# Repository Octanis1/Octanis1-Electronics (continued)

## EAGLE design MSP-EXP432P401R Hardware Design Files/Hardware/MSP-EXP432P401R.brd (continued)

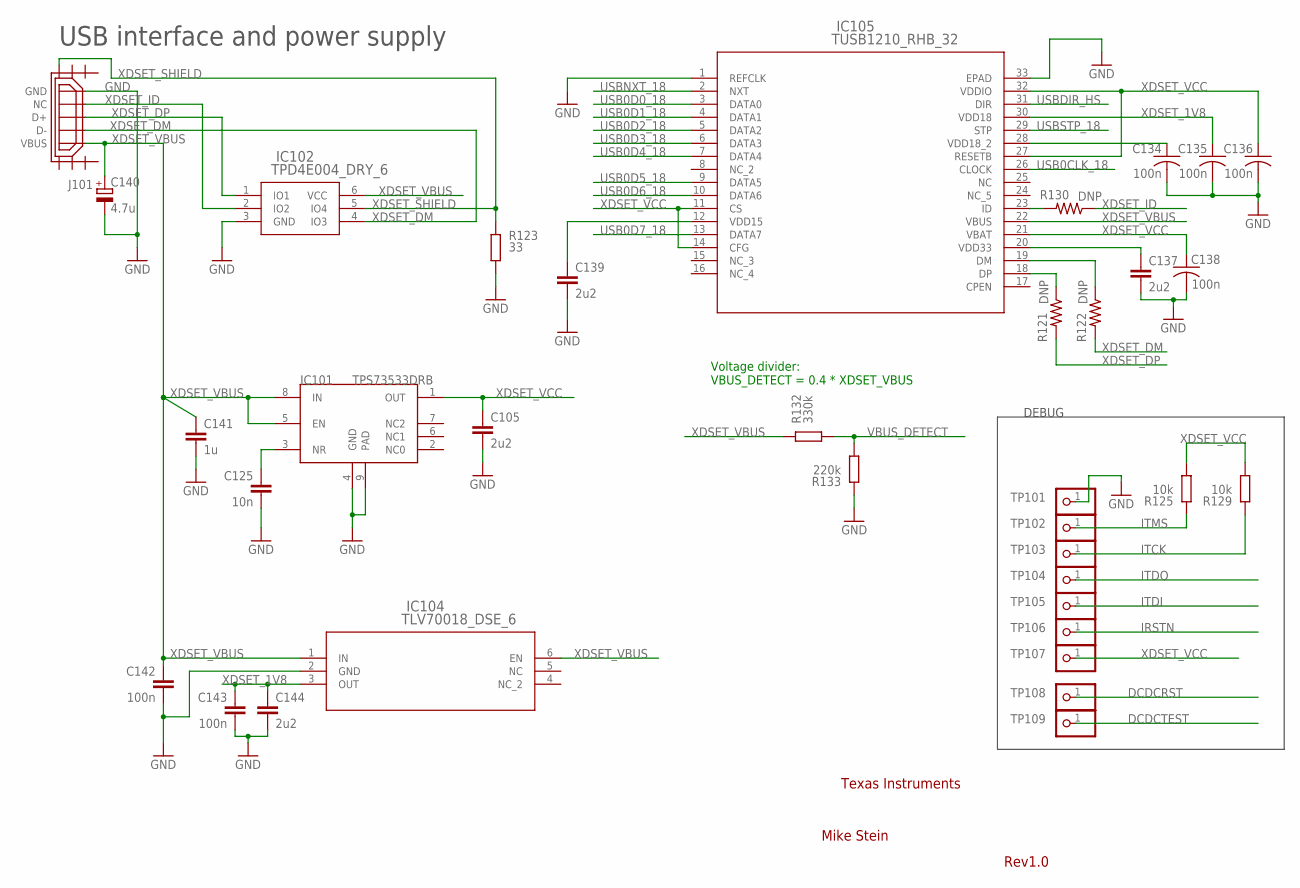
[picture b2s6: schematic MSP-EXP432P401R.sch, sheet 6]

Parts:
C105, C137, C139, C144: 2u2; C0603
C125: 10n; 0402
C134, C135, C136, C138: 100n; C0402
C140: 4.7u; A/3216-18R
C141: 1u; C0603
C142, C143: 100n; 0402
IC101: TPS73533DRB; SON8
IC102: TPD4E004_DRY_6; DRY6
IC104: TLV70018_DSE_6; DSE6
IC105: TUSB1210_RHB_32; RHB32_3P45X3P45
J101: USB_MICRO_FLIPPED; HIROSE-ZX62R-B-5P
R121, R122, R130: DNP; R0402
R123: 33; 0402
R125, R129: 10k; 0402
R132: 330k; 0402
R133: 220k; 0402
TP101, TP102, TP103, TP104, TP105, TP106, TP107, TP108, TP109: TEST_PIN2; 1X01

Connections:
DCDCRST: TP108.1; also elsewhere on the board
DCDCTEST: TP109.1; also elsewhere on the board
GND: C105.2, C125.2, C134.2, C135.2, C136.2, C137.2, C138.2, C139.2, C140.-, C141.2, C142.2, C143.2, C144.2, IC101.4 (GND), IC101.9 (PAD), IC102.3 (GND), IC104.2 (GND), IC105.1 (REFCLK), IC105.33 (EPAD), J101.GND, R123.2, R133.1, TP101.1; also elsewhere on the board
IRSTN: TP106.1; also elsewhere on the board
ITCK: R129.1, TP103.1; also elsewhere on the board
ITDI: TP105.1; also elsewhere on the board
ITDO: TP104.1; also elsewhere on the board
ITMS: R125.1, TP102.1; also elsewhere on the board
unnamed: IC105.18 (DP), R121.1
unnamed: IC105.19 (DM), R122.1
unnamed: C125.1, IC101.3 (NR)
unnamed: C137.1, IC105.20 (VDD33)
unnamed: C139.1, IC105.12 (VDD15)
unnamed: C134.1, IC105.28 (VDD18_2)
USB0CLK_18: IC105.26 (CLOCK); also elsewhere on the board
USB0D0_18: IC105.3 (DATA0); also elsewhere on the board
USB0D1_18: IC105.4 (DATA1); also elsewhere on the board
USB0D2_18: IC105.5 (DATA2); also elsewhere on the board
USB0D3_18: IC105.6 (DATA3); also elsewhere on the board
USB0D4_18: IC105.7 (DATA4); also elsewhere on the board
USB0D5_18: IC105.9 (DATA5); also elsewhere on the board
USB0D6_18: IC105.10 (DATA6); also elsewhere on the board
USB0D7_18: IC105.13 (DATA7); also elsewhere on the board
USBDIR_HS: IC105.31 (DIR); also elsewhere on the board
USBNXT_18: IC105.2 (NXT); also elsewhere on the board
USBSTP_18: IC105.29 (STP); also elsewhere on the board
VBUS_DETECT: R132.2, R133.2; also elsewhere on the board
XDSET_1V8: C135.1, C143.1, C144.1, IC104.3 (OUT), IC105.30 (VDD18); also elsewhere on the board
XDSET_DM: IC102.4 (IO3), J101.D-, R122.2; also elsewhere on the board
XDSET_DP: IC102.1 (IO1), J101.D+, R121.2; also elsewhere on the board
XDSET_ID: IC102.2 (IO2), J101.NC, R130.1; also elsewhere on the board
XDSET_IDR: IC105.23 (ID), R130.2
XDSET_SHIELD: IC102.5 (IO4), J101.SHIELD3, R123.1
XDSET_VBUS: C140.+, C141.1, C142.1, IC101.5 (EN), IC101.8 (IN), IC102.6 (VCC), IC104.1 (IN), IC104.6 (EN), IC105.22 (VBUS), J101.VBUS, R132.1; also elsewhere on the board
XDSET_VCC: C105.1, C136.1, C138.1, IC101.1 (OUT), IC105.11 (CS), IC105.14 (CFG), IC105.21 (VBAT), IC105.27 (RESETB), IC105.32 (VDDIO), R125.2, R129.2, TP107.1; also elsewhere on the board

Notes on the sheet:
USB interface and power supply
DEBUG
Voltage divider: VBUS_DETECT = 0.4 * XDSET_VBUS
Texas Instruments
Mike Stein
Rev1.0

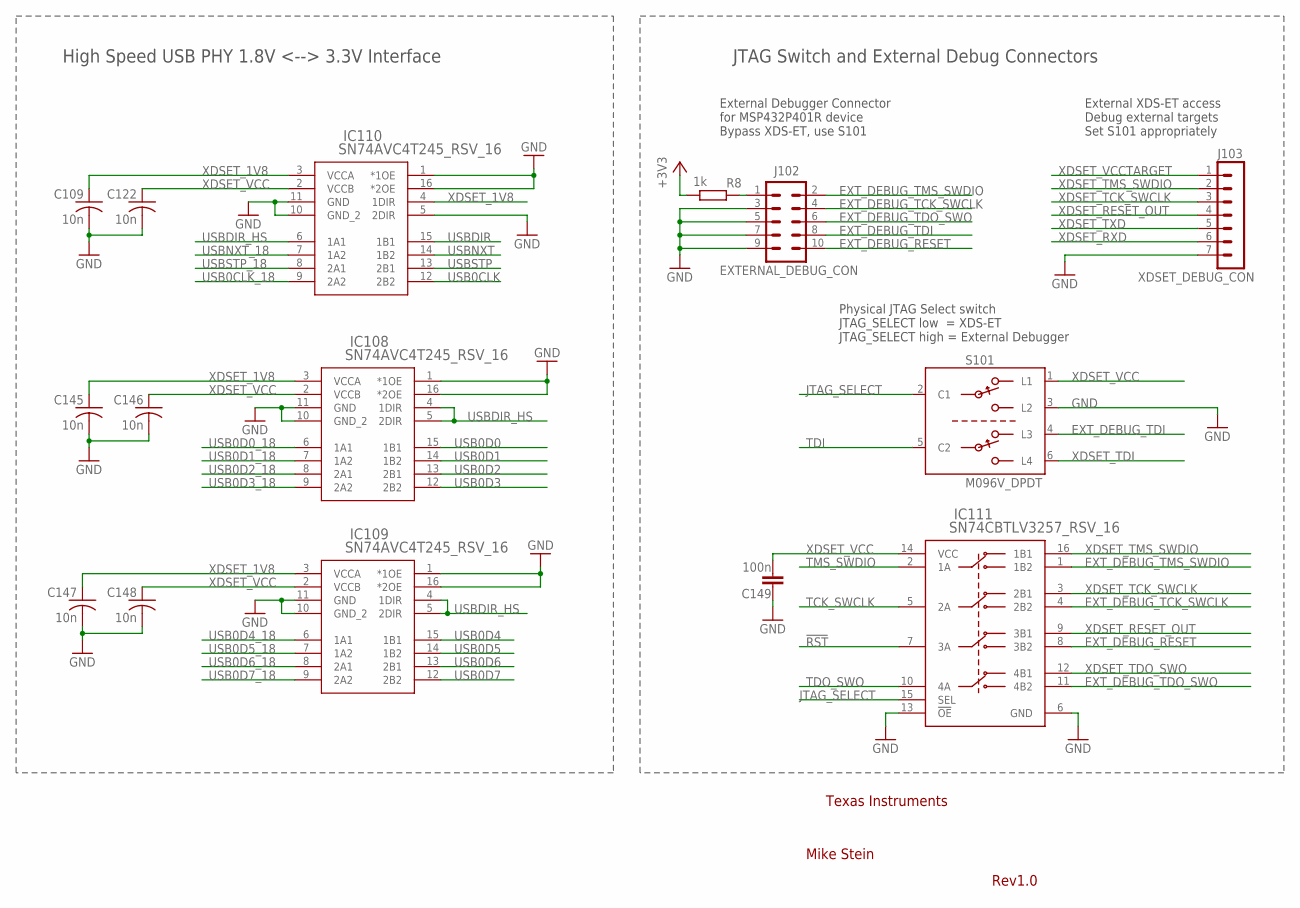
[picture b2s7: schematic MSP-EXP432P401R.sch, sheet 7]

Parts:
C109, C122, C145, C146, C147, C148: 10n; C0402
C149: 100n; 0402
IC108, IC109, IC110: SN74AVC4T245_RSV_16; RSV16
IC111: SN74CBTLV3257_RSV_16; RSV16
J102: EXTERNAL_DEBUG_CON; EXTERNAL_DEBUG
J103: XDSET_DEBUG_CON; XDSET_DEBUG
R8: 1k; 0402
S101: M096V_DPDT

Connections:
!RST: IC111.7 (3A); also elsewhere on the board
+3V3: R8.1; also elsewhere on the board
EXT_DEBUG_RESET: IC111.8 (3B2), J102.10
EXT_DEBUG_TCK_SWCLK: IC111.4 (2B2), J102.4
EXT_DEBUG_TDI: J102.8, S101.4 (L3)
EXT_DEBUG_TDO_SWO: IC111.11 (4B2), J102.6
EXT_DEBUG_TMS_SWDIO: IC111.1 (1B2), J102.2
GND: C109.2, C122.2, C145.2, C146.2, C147.2, C148.2, C149.2, IC108.1 (*1OE), IC108.10 (GND_2), IC108.11 (GND), IC108.16 (*2OE), IC109.1 (*1OE), IC109.10 (GND_2), IC109.11 (GND), IC109.16 (*2OE), IC110.1 (*1OE), IC110.5 (2DIR), IC110.10 (GND_2), IC110.11 (GND), IC110.16 (*2OE), IC111.6 (GND), IC111.13 (!OE), J102.3, J102.5, J102.7, J102.9, J103.7, S101.3 (L2); also elsewhere on the board
JTAG_SELECT: IC111.15 (SEL), S101.2 (C1)
unnamed: J102.1, R8.2
TCK_SWCLK: IC111.5 (2A); also elsewhere on the board
TDI: S101.5 (C2); also elsewhere on the board
TDO_SWO: IC111.10 (4A); also elsewhere on the board
TMS_SWDIO: IC111.2 (1A); also elsewhere on the board
USB0CLK: IC110.12 (2B2); also elsewhere on the board
USB0CLK_18: IC110.9 (2A2); also elsewhere on the board
USB0D0: IC108.15 (1B1); also elsewhere on the board
USB0D0_18: IC108.6 (1A1); also elsewhere on the board
USB0D1: IC108.14 (1B2); also elsewhere on the board
USB0D1_18: IC108.7 (1A2); also elsewhere on the board
USB0D2: IC108.13 (2B1); also elsewhere on the board
USB0D2_18: IC108.8 (2A1); also elsewhere on the board
USB0D3: IC108.12 (2B2); also elsewhere on the board
USB0D3_18: IC108.9 (2A2); also elsewhere on the board
USB0D4: IC109.15 (1B1); also elsewhere on the board
USB0D4_18: IC109.6 (1A1); also elsewhere on the board
USB0D5: IC109.14 (1B2); also elsewhere on the board
USB0D5_18: IC109.7 (1A2); also elsewhere on the board
USB0D6: IC109.13 (2B1); also elsewhere on the board
USB0D6_18: IC109.8 (2A1); also elsewhere on the board
USB0D7: IC109.12 (2B2); also elsewhere on the board
USB0D7_18: IC109.9 (2A2); also elsewhere on the board
USBDIR: IC110.15 (1B1); also elsewhere on the board
USBDIR_HS: IC108.4 (1DIR), IC108.5 (2DIR), IC109.4 (1DIR), IC109.5 (2DIR), IC110.6 (1A1); also elsewhere on the board
USBNXT: IC110.14 (1B2); also elsewhere on the board
USBNXT_18: IC110.7 (1A2); also elsewhere on the board
USBSTP: IC110.13 (2B1); also elsewhere on the board
USBSTP_18: IC110.8 (2A1); also elsewhere on the board
XDSET_1V8: C109.1, C145.1, C147.1, IC108.3 (VCCA), IC109.3 (VCCA), IC110.3 (VCCA), IC110.4 (1DIR); also elsewhere on the board
XDSET_RESET_OUT: IC111.9 (3B1), J103.4; also elsewhere on the board
XDSET_RXD: J103.6; also elsewhere on the board
XDSET_TCK_SWCLK: IC111.3 (2B1), J103.3; also elsewhere on the board
XDSET_TDI: S101.6 (L4); also elsewhere on the board
XDSET_TDO_SWO: IC111.12 (4B1); also elsewhere on the board
XDSET_TMS_SWDIO: IC111.16 (1B1), J103.2; also elsewhere on the board
XDSET_TXD: J103.5; also elsewhere on the board
XDSET_VCC: C122.1, C146.1, C148.1, C149.1, IC108.2 (VCCB), IC109.2 (VCCB), IC110.2 (VCCB), IC111.14 (VCC), S101.1 (L1); also elsewhere on the board
XDSET_VCCTARGET: J103.1; also elsewhere on the board

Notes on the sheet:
High Speed USB PHY 1.8V <--> 3.3V Interface
External Debugger Connector for MSP432P401R device Bypass XDS-ET, use S101
External XDS-ET access Debug external targets Set S101 appropriately
Physical JTAG Select switch JTAG_SELECT low = XDS-ET JTAG_SELECT high = External Debugger
JTAG Switch and External Debug Connectors
Texas Instruments
Mike Stein
Rev1.0

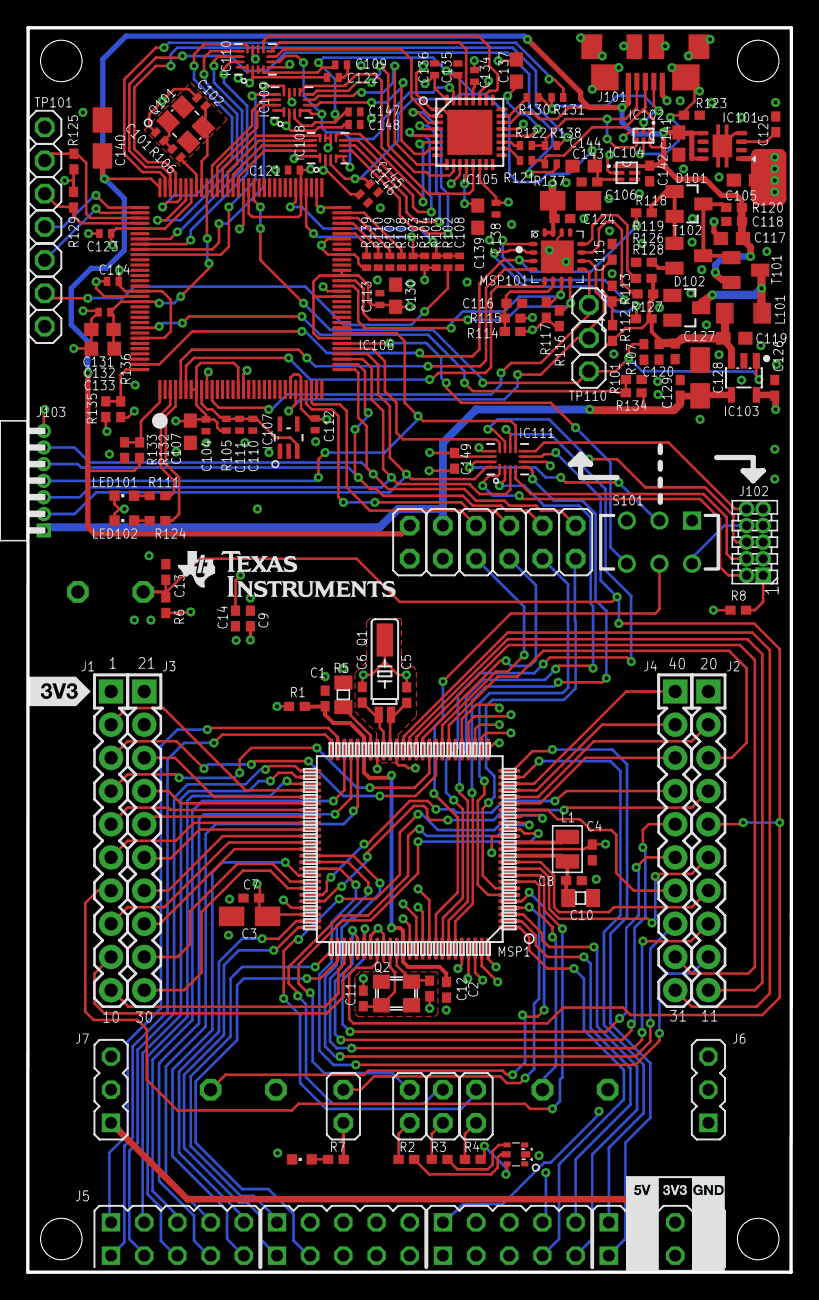
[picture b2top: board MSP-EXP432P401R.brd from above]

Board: 4 copper layers, 58.4 x 95.2 mm, 179 parts (0 on the bottom side), 200 nets.

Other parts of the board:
DRAW3: LOGO-ROCKET-10X7MM-BRD
U$4: LOGO16_TPLACE

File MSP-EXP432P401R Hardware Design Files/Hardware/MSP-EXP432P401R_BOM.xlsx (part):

BOM for MSP-EXP432P401R
Do not populate (Dnp) part if Quantity equals zero
Use exact PartNumber and Manufacturer if this data is provided
Feedback from CM needed where supplier equals CM
 | Qty | Reference | Manufacturer | Description | Part Number | PCB Decal/Package | Value | Supplier1 | Digikey Number | Comment
 | 1 | C1 | Standard | CAP CER 0.1UF 10V 20% X5R 0402,Digikey 445-4984-1-ND |  | 402 | 100n | Digikey | 445-4984-1-ND
 | 1 | C2 | Standard | CAP CER 0.1UF 10V 20% X5R 0402,Digikey 445-4984-1-ND |  | 402 | 100n | Digikey | 445-4984-1-ND
 | 1 | C3 | Standard | CAP TANT 10UF 10V 20% 1206,Digikey 493-2351-1-ND |  | TANT_3216 | 10u | Digikey | 493-2351-1-ND
 | 1 | C4 | Standard | CAP CER 0.1UF 10V 20% X5R 0402,Digikey 445-4984-1-ND |  | 402 | 100n | Digikey | 445-4984-1-ND
 | 1 | C5 | Standard | CAP CER 12PF 50V 5% NP0 0402,Digikey 445-1236-1-ND |  | 402 | 12p | Digikey | 445-1236-1-ND
 | 1 | C6 | Standard | CAP CER 12PF 50V 5% NP0 0402,Digikey 445-1236-1-ND |  | 402 | 12p | Digikey | 445-1236-1-ND
 | 1 | C7 | Standard | CAP CER 0.1UF 10V 20% X5R 0402,Digikey 445-4984-1-ND |  | 402 | 100n | Digikey | 445-4984-1-ND
 | 1 | C8 | Standard | CAP CER 0.1UF 10V 20% X5R 0402,Digikey 445-4984-1-ND |  | 402 | 100n | Digikey | 445-4984-1-ND
 | 1 | C9 | Standard | CAP CER 0.1UF 10V 20% X5R 0402,Digikey 445-4984-1-ND |  | 402 | 100n | Digikey | 445-4984-1-ND
 | 1 | C10 | Standard | CAP CER 4.7UF 10V Y5V 0805, Digikey 445-1370-1-ND |  | 805 | 4.7u | Digikey | 445-1370-1-ND
 | 1 | C11 | Standard | CAP CER 22PF 50V 5% NP0 0402, Digikey 445-1239-1-ND |  | 402 | 22p | Digikey | 445-1239-1-ND
 | 1 | C12 | Standard | CAP CER 22PF 50V 5% NP0 0402, Digikey 445-1239-1-ND |  | 402 | 22p | Digikey | 445-1239-1-ND
 | 1 | C13 | Standard | CAP CER 1000PF 50V 10% X7R 0402,Digikey 445-1256-1-ND |  | 402 | 1n | Digikey | 445-1256-1-ND
 | 1 | C14 | Standard | CAP CER 0.1UF 10V 20% X5R 0402,Digikey 445-4984-1-ND |  | 402 | 100n | Digikey | 445-4984-1-ND
 | 1 | C101 | Standard | CAP CER 12PF 50V 5% NP0 0402,Digikey 445-1236-1-ND |  | 402 | 12p | Digikey | 445-1236-1-ND
 | 1 | C102 | Standard | CAP CER 12PF 50V 5% NP0 0402,Digikey 445-1236-1-ND |  | 402 | 12p | Digikey | 445-1236-1-ND
 | 1 | C103 | Standard | CAP CER 0.1UF 10V 20% X5R 0402,Digikey 445-4984-1-ND |  | 402 | 100n | Digikey | 445-4984-1-ND
 | 1 | C104 | Standard | CAP CER 10000PF 10V 10% X7R 0402, Digikey 478-7890-1-ND |  | 402 | 10n | Digikey | 478-7890-1-ND
 | 1 | C105 | Standard | CAP CER 2.2UF 10V 10% X5R 0603, Digikey 587-1253-1-ND |  | 603 | 2.2u | Digikey | 587-1253-1-ND
 | 1 | C106 | Standard | CAP TANT 4.7UF 10V 10% 1206,Digikey 478-8221-1-ND |  | TANT_3216 | 4.7u | Digikey | 478-8221-1-ND
 | 1 | C107 | Standard | CAP CER 1UF 10V 10% X5R 0603, Digikey 445-1321-1-ND |  | 603 | 1u | Digikey | 445-1321-1-ND
 | 0 | C108 | Standard |  |  | 402 | dnp
 | 1 | C109 | Standard | CAP CER 10000PF 10V 10% X7R 0402, Digikey 478-7890-1-ND |  | 402 | 10n | Digikey | 478-7890-1-ND
 | 1 | C110 | Standard | CAP CER 10000PF 10V 10% X7R 0402, Digikey 478-7890-1-ND |  | 402 | 10n | Digikey | 478-7890-1-ND
 | 1 | C111 | Standard | CAP CER 0.1UF 10V 20% X5R 0402,Digikey 445-4984-1-ND |  | 402 | 100n | Digikey | 445-4984-1-ND
 | 1 | C112 | Standard | CAP CER 10000PF 10V 10% X7R 0402, Digikey 478-7890-1-ND |  | 402 | 10n | Digikey | 478-7890-1-ND
 | 1 | C113 | Standard | CAP CER 0.1UF 10V 20% X5R 0402,Digikey 445-4984-1-ND |  | 402 | 100n | Digikey | 445-4984-1-ND
 | 1 | C114 | Standard | CAP CER 10000PF 10V 10% X7R 0402, Digikey 478-7890-1-ND |  | 402 | 10n | Digikey | 478-7890-1-ND
 | 1 | C115 | Standard | CAP CER 33PF 50V 5% NP0 0402,Digikey 445-1241-1-ND |  | 402 | 33p | Digikey | 445-1241-1-ND
 | 1 | C116 | Standard | CAP CER 33PF 50V 5% NP0 0402,Digikey 445-1241-1-ND |  | 402 | 33p | Digikey | 445-1241-1-ND
 | 1 | C117 | Standard | CAP CER 4.7UF 10V 10% X5R 0603,Digikey 445-5170-1-ND |  | 603 | 4.7u | Digikey | 445-5170-1-ND
 | 1 | C118 | Standard | CAP CER 0.1UF 10V 20% X5R 0402,Digikey 445-4984-1-ND |  | 402 | 100n | Digikey | 445-4984-1-ND
 | 1 | C119 | TDK | CAP CER 4.7UF 10V 10% X5R 0603, Digikey 445-5170-1-ND | C1608X5R1A475K080AC | 603 | 4.7u | Digikey | 445-5170-1-ND
 | 1 | C120 | Standard | CAP CER 0.1UF 10V 20% X5R 0402,Digikey 445-4984-1-ND |  | 402 | 100n | Digikey | 445-4984-1-ND
 | 1 | C121 | Standard | CAP CER 0.1UF 10V 20% X5R 0402,Digikey 445-4984-1-ND |  | 402 | 100n | Digikey | 445-4984-1-ND
 | 1 | C122 | Standard | CAP CER 10000PF 10V 10% X7R 0402, Digikey 478-7890-1-ND |  | 402 | 10n | Digikey | 478-7890-1-ND
 | 1 | C123 | Standard | CAP CER 10000PF 10V 10% X7R 0402, Digikey 478-7890-1-ND |  | 402 | 10n | Digikey | 478-7890-1-ND
 | 1 | C124 | Standard | CAP CER 0.1UF 10V 20% X5R 0402,Digikey 445-4984-1-ND |  | 402 | 100n | Digikey | 445-4984-1-ND
 | 1 | C125 | Standard | CAP CER 10000PF 10V 10% X7R 0402, Digikey 478-7890-1-ND |  | 402 | 10n | Digikey | 478-7890-1-ND
 | 1 | C126 | Standard | CAP CER 0.22UF 16V 10% X5R 0402,Digikey 445-4972-1-ND |  | 402 | 220n | Digikey | 445-4972-1-ND
 | 1 | C127 | Standard | CAP CER 0.22UF 16V 10% X5R 0402,Digikey 445-4972-1-ND |  | 402 | 220n | Digikey | 445-4972-1-ND
 | 1 | C128 | Standard | CAP CER 47UF 10V 20% X5R 1206, Digikey 445-6006-1-ND |  | TANT_3216 | 47u | Digikey | 445-6006-1-ND
 | 1 | C129 | Standard | CAP CER 0.1UF 10V 20% X5R 0402,Digikey 445-4984-1-ND |  | 402 | 100n | Digikey | 445-4984-1-ND
 | 1 | C130 | Standard | CAP CER 1UF 10V 10% X5R 0603, Digikey 445-1321-1-ND |  | 603 | 1u | Digikey | 445-1321-1-ND
 | 1 | C131 | Standard | CAP CER 0.1UF 10V 20% X5R 0402,Digikey 445-4984-1-ND |  | 402 | 100n | Digikey | 445-4984-1-ND
 | 1 | C132 | Standard | CAP CER 1UF 10V 10% X5R 0603, Digikey 445-1321-1-ND |  | 603 | 1u | Digikey | 445-1321-1-ND
 | 1 | C133 | Standard | CAP CER 2.2UF 10V 10% X5R 0603, Digikey 587-1253-1-ND |  | 603 | 2.2u | Digikey | 587-1253-1-ND
 | 1 | C134 | Standard | CAP CER 0.1UF 10V 20% X5R 0402,Digikey 445-4984-1-ND |  | 402 | 100n | Digikey | 445-4984-1-ND
 | 1 | C135 | Standard | CAP CER 0.1UF 10V 20% X5R 0402,Digikey 445-4984-1-ND |  | 402 | 100n | Digikey | 445-4984-1-ND
 | 1 | C136 | Standard | CAP CER 0.1UF 10V 20% X5R 0402,Digikey 445-4984-1-ND |  | 402 | 100n | Digikey | 445-4984-1-ND
 | 1 | C137 | Standard | CAP CER 2.2UF 10V 10% X5R 0603, Digikey 587-1253-1-ND |  | 603 | 2.2u | Digikey | 587-1253-1-ND
 | 1 | C138 | Standard | CAP CER 0.1UF 10V 20% X5R 0402,Digikey 445-4984-1-ND |  | 402 | 100n | Digikey | 445-4984-1-ND
 | 1 | C139 | Standard | CAP CER 2.2UF 10V 10% X5R 0603, Digikey 587-1253-1-ND |  | 603 | 2.2u | Digikey | 587-1253-1-ND
 | 1 | C140 | Standard | CAP TANT 4.7UF 10V 10% 1206,Digikey 478-8221-1-ND |  | TANT_3216 | 4.7u | Digikey | 478-8221-1-ND
 | 1 | C141 | Standard | CAP CER 1UF 10V 10% X5R 0603, Digikey 445-1321-1-ND |  | 603 | 1u | Digikey | 445-1321-1-ND
 | 1 | C142 | Standard | CAP CER 0.1UF 10V 20% X5R 0402,Digikey 445-4984-1-ND |  | 402 | 100n | Digikey | 445-4984-1-ND
 | 1 | C143 | Standard | CAP CER 0.1UF 10V 20% X5R 0402,Digikey 445-4984-1-ND |  | 402 | 100n | Digikey | 445-4984-1-ND
 | 1 | C144 | Standard | CAP CER 2.2UF 10V 10% X5R 0603, Digikey 587-1253-1-ND |  | 603 | 2.2u | Digikey | 587-1253-1-ND
 | 1 | C145 | Standard | CAP CER 10000PF 10V 10% X7R 0402, Digikey 478-7890-1-ND |  | 402 | 10n | Digikey | 478-7890-1-ND
 | 1 | C146 | Standard | CAP CER 10000PF 10V 10% X7R 0402, Digikey 478-7890-1-ND |  | 402 | 10n | Digikey | 478-7890-1-ND
 | 1 | C147 | Standard | CAP CER 10000PF 10V 10% X7R 0402, Digikey 478-7890-1-ND |  | 402 | 10n | Digikey | 478-7890-1-ND
 | 1 | C148 | Standard | CAP CER 10000PF 10V 10% X7R 0402, Digikey 478-7890-1-ND |  | 402 | 10n | Digikey | 478-7890-1-ND
 | 1 | C149 | Standard | CAP CER 0.1UF 10V 20% X5R 0402,Digikey 445-4984-1-ND |  | 402 | 100n | Digikey | 445-4984-1-ND
 | 1 | D101 | NXP | DIODE SCHOTTKY 40V 120MA TO236AB,Digikey 568-4862-1-ND | BAS40-05 215 | SOT-23 | BAS40-05 | Digikey | 568-4862-1-ND
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
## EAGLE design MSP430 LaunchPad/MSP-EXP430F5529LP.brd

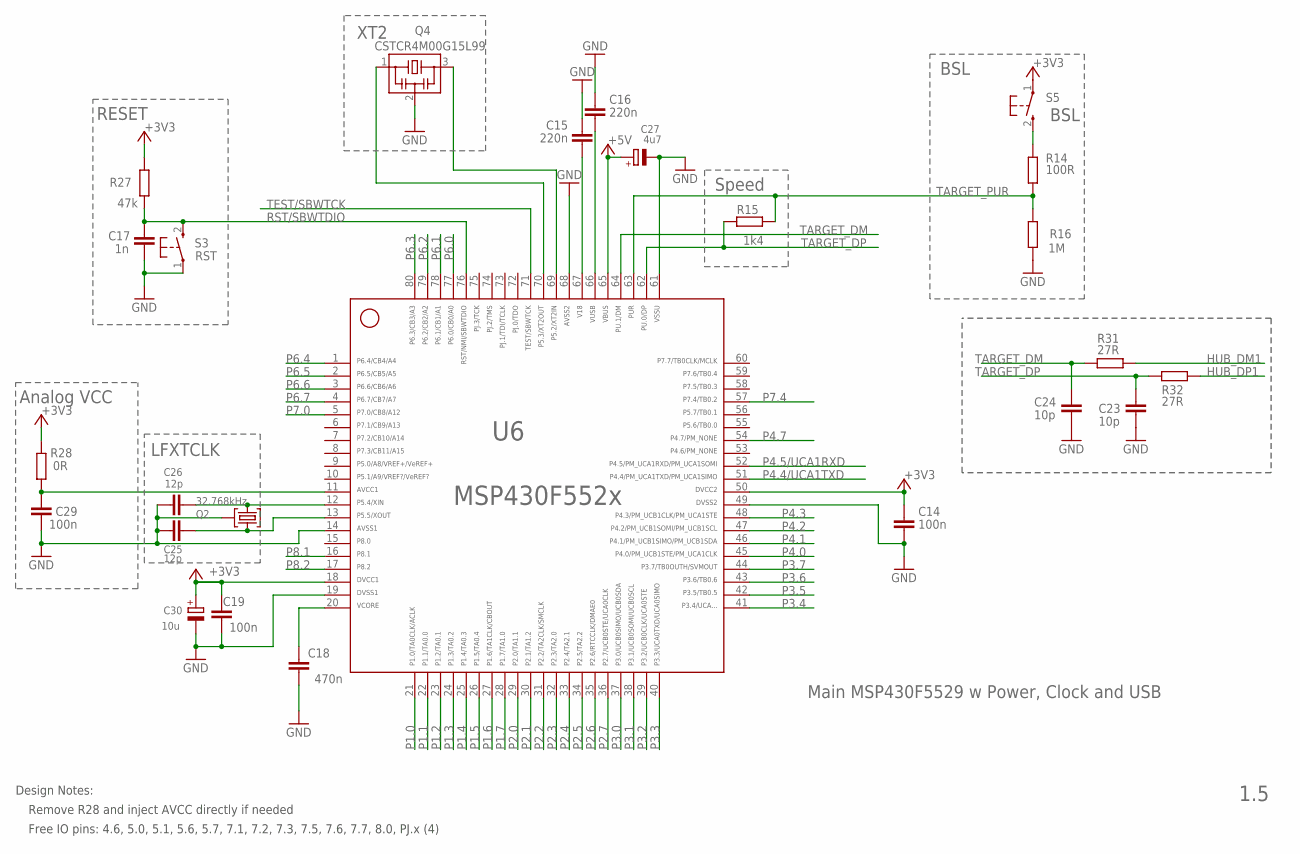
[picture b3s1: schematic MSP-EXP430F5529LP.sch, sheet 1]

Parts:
C14, C19, C29: 100n; C0402
C15, C16: 220n; C0402
C17: 1n; C0402
C18: 470n; C0402
C23, C24: 10p; C0402
C25, C26: 12p; C0402
C27: 4u7; A/3216-18R
C30: 10u; A/3216-18R
Q2: 32.768kHz; MS3V-T1R
Q4: CSTCR4M00G15L99; MURATA-FILTER_CSTCR
R14: 100R; R0402
R15: 1k4; R0402
R16: 1M; R0402
R27: 47k; R0402
R28: 0R; R0402
R31, R32: 27R; R0402
S3: RST; PBTH
S5: BSL; PBTH
U6: MSP430F5529IPNR; PN80

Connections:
+3V3: C14.1, C19.2, C30.+, R27.2, R28.2, S5.1, U6.18, U6.50; also elsewhere on the board
+5V: C27.+, U6.65; also elsewhere on the board
AVCC: C29.1, R28.1, U6.11
GND: C14.2, C15.2, C16.2, C17.2, C18.1, C19.1, C23.2, C24.2, C25.1, C26.1, C27.-, C29.2, C30.-, Q2.P3 (GND), Q4.2, R16.1, S3.1, U6.14, U6.19, U6.49, U6.61, U6.68; also elsewhere on the board
HUB_DM1: R31.1; also elsewhere on the board
HUB_DP1: R32.1; also elsewhere on the board
unnamed: R14.1, S5.2 (S)
P1.0: U6.21; also elsewhere on the board
P1.1: U6.22; also elsewhere on the board
P1.2: U6.23; also elsewhere on the board
P1.3: U6.24; also elsewhere on the board
P1.4: U6.25; also elsewhere on the board
P1.5: U6.26; also elsewhere on the board
P1.6: U6.27; also elsewhere on the board
P1.7: U6.28; also elsewhere on the board
P2.0: U6.29; also elsewhere on the board
P2.1: U6.30; also elsewhere on the board
P2.2: U6.31; also elsewhere on the board
P2.3: U6.32; also elsewhere on the board
P2.4: U6.33; also elsewhere on the board
P2.5: U6.34; also elsewhere on the board
P2.6: U6.35; also elsewhere on the board
P2.7: U6.36; also elsewhere on the board
P3.0: U6.37; also elsewhere on the board
P3.1: U6.38; also elsewhere on the board
P3.2: U6.39; also elsewhere on the board
P3.3: U6.40; also elsewhere on the board
P3.4: U6.41; also elsewhere on the board
P3.5: U6.42; also elsewhere on the board
P3.6: U6.43; also elsewhere on the board
P3.7: U6.44; also elsewhere on the board
P4.0: U6.45; also elsewhere on the board
P4.1: U6.46; also elsewhere on the board
P4.2: U6.47; also elsewhere on the board
P4.3: U6.48; also elsewhere on the board
P4.4/UCA1TXD: U6.51; also elsewhere on the board
P4.5/UCA1RXD: U6.52; also elsewhere on the board
P4.7: U6.54; also elsewhere on the board
P5.2/XT2IN: Q4.3, U6.69
P5.3/XT2OUT: Q4.1, U6.70
P5.4/XIN: C26.2, Q2.P2 (2), U6.12
P5.5/XOUT: C25.2, Q2.P1 (1), U6.13
P6.0: U6.77; also elsewhere on the board
P6.1: U6.78; also elsewhere on the board
P6.2: U6.79; also elsewhere on the board
P6.3: U6.80; also elsewhere on the board
P6.4: U6.1; also elsewhere on the board
P6.5: U6.2; also elsewhere on the board
P6.6: U6.3; also elsewhere on the board
P6.7: U6.4; also elsewhere on the board
P7.0: U6.5; also elsewhere on the board
P7.4: U6.57; also elsewhere on the board
P8.1: U6.16; also elsewhere on the board
P8.2: U6.17; also elsewhere on the board
RST/SBWTDIO: C17.1, R27.1, S3.2 (S), U6.76; also elsewhere on the board
TARGET_DM: C24.1, R31.2, U6.64
TARGET_DP: C23.1, R15.2, R32.2, U6.62
TARGET_PUR: R14.2, R15.1, R16.2, U6.63
TARGET_VUSB: C16.1, U6.66
TEST/SBWTCK: U6.71; also elsewhere on the board
V18: C15.1, U6.67
VCORE: C18.2, U6.20

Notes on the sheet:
RESET
LFXTCLK
XT2
Main MSP430F5529 w Power, Clock and USB
1.5
BSL
Speed
Analog VCC
Remove R28 and inject AVCC directly if needed
Design Notes:
Free IO pins: 4.6, 5.0, 5.1, 5.6, 5.7, 7.1, 7.2, 7.3, 7.5, 7.6, 7.7, 8.0, PJ.x (4)

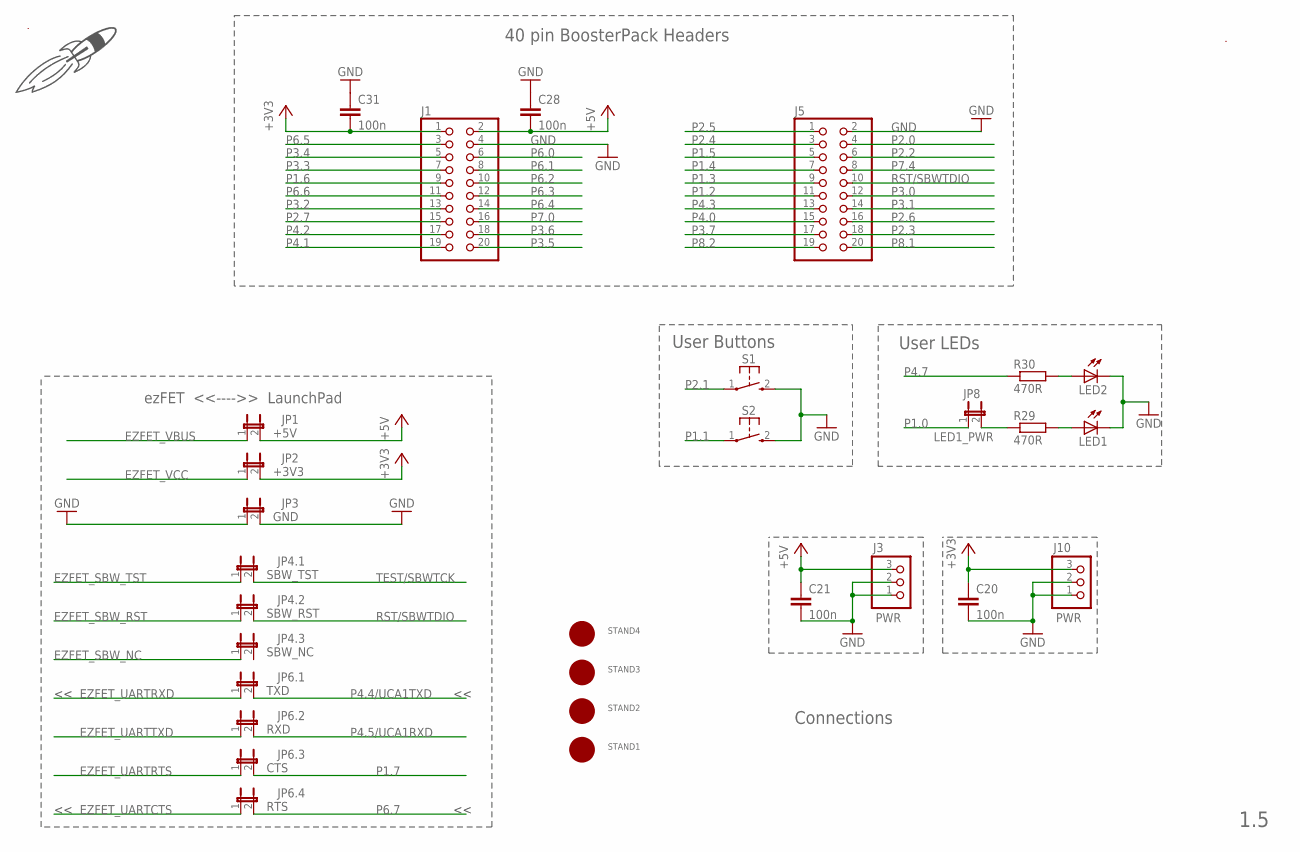
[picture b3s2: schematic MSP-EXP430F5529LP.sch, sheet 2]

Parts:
C20, C21, C28, C31: 100n; C0402
DRAW1: LOGO-ROCKET-20X13MM-SCH-S; LOGO-ROCKET-10X7MM-BRD
J1, J5: PINHD-2X10; 2X10
J3, J10: PWR; 1X03
JP1: +5V; JP1M
JP2: +3V3; JP1M
JP3: GND; JP1M
JP4.1: SBW_TST; JP1M
JP4.2: SBW_RST; JP1M
JP4.3: SBW_NC; JP1M
JP6.1: TXD; JP1M
JP6.2: RXD; JP1M
JP6.3: CTS; JP1M
JP6.4: RTS; JP1M
JP8: LED1_PWR; JP1
LED1, LED2: LEDCHIPLED_0603; CHIPLED_0603
R29, R30: 470R; R0402
S1, S2: PB; PBTH
STAND1, STAND2, STAND3, STAND4: MOUNT; MOUNTHOLE_110MIL
U$3: 5529_REAR_SILK_REV1_5_FINAL
U$4: MS_TM

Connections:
+3V3: C20.1, C31.2, J1.1, J10.3, JP2.2; also elsewhere on the board
+5V: C21.1, C28.2, J1.2, J3.3, JP1.2; also elsewhere on the board
EZFET_SBW_NC: JP4.3.1; also elsewhere on the board
EZFET_SBW_RST: JP4.2.1; also elsewhere on the board
EZFET_SBW_TST: JP4.1.1; also elsewhere on the board
EZFET_UARTCTS: JP6.4.1; also elsewhere on the board
EZFET_UARTRTS: JP6.3.1; also elsewhere on the board
EZFET_UARTRXD: JP6.1.1; also elsewhere on the board
EZFET_UARTTXD: JP6.2.1; also elsewhere on the board
EZFET_VBUS: JP1.1; also elsewhere on the board
EZFET_VCC: JP2.1; also elsewhere on the board
GND: C20.2, C21.2, C28.1, C31.1, J1.4, J3.1, J3.2, J5.2, J10.1, J10.2, JP3.1, JP3.2, LED1.C, LED2.C, S1.2 (S), S2.2 (S); also elsewhere on the board
unnamed: JP8.2, R29.1
unnamed: LED1.A, R29.2
unnamed: LED2.A, R30.2
P1.0: JP8.1; also elsewhere on the board
P1.1: S2.1; also elsewhere on the board
P1.2: J5.11; also elsewhere on the board
P1.3: J5.9; also elsewhere on the board
P1.4: J5.7; also elsewhere on the board
P1.5: J5.5; also elsewhere on the board
P1.6: J1.9; also elsewhere on the board
P1.7: JP6.3.2; also elsewhere on the board
P2.0: J5.4; also elsewhere on the board
P2.1: S1.1; also elsewhere on the board
P2.2: J5.6; also elsewhere on the board
P2.3: J5.18; also elsewhere on the board
P2.4: J5.3; also elsewhere on the board
P2.5: J5.1; also elsewhere on the board
P2.6: J5.16; also elsewhere on the board
P2.7: J1.15; also elsewhere on the board
P3.0: J5.12; also elsewhere on the board
P3.1: J5.14; also elsewhere on the board
P3.2: J1.13; also elsewhere on the board
P3.3: J1.7; also elsewhere on the board
P3.4: J1.5; also elsewhere on the board
P3.5: J1.20; also elsewhere on the board
P3.6: J1.18; also elsewhere on the board
P3.7: J5.17; also elsewhere on the board
P4.0: J5.15; also elsewhere on the board
P4.1: J1.19; also elsewhere on the board
P4.2: J1.17; also elsewhere on the board
P4.3: J5.13; also elsewhere on the board
P4.4/UCA1TXD: JP6.1.2; also elsewhere on the board
P4.5/UCA1RXD: JP6.2.2; also elsewhere on the board
P4.7: R30.1; also elsewhere on the board
P6.0: J1.6; also elsewhere on the board
P6.1: J1.8; also elsewhere on the board
P6.2: J1.10; also elsewhere on the board
P6.3: J1.12; also elsewhere on the board
P6.4: J1.14; also elsewhere on the board
P6.5: J1.3; also elsewhere on the board
P6.6: J1.11; also elsewhere on the board
P6.7: JP6.4.2; also elsewhere on the board
P7.0: J1.16; also elsewhere on the board
P7.4: J5.8; also elsewhere on the board
P8.1: J5.20; also elsewhere on the board
P8.2: J5.19; also elsewhere on the board
RST/SBWTDIO: J5.10, JP4.2.2; also elsewhere on the board
TEST/SBWTCK: JP4.1.2; also elsewhere on the board

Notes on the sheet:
40 pin BoosterPack Headers
Connections
1.5
User LEDs
User Buttons
ezFET <<---->> LaunchPad

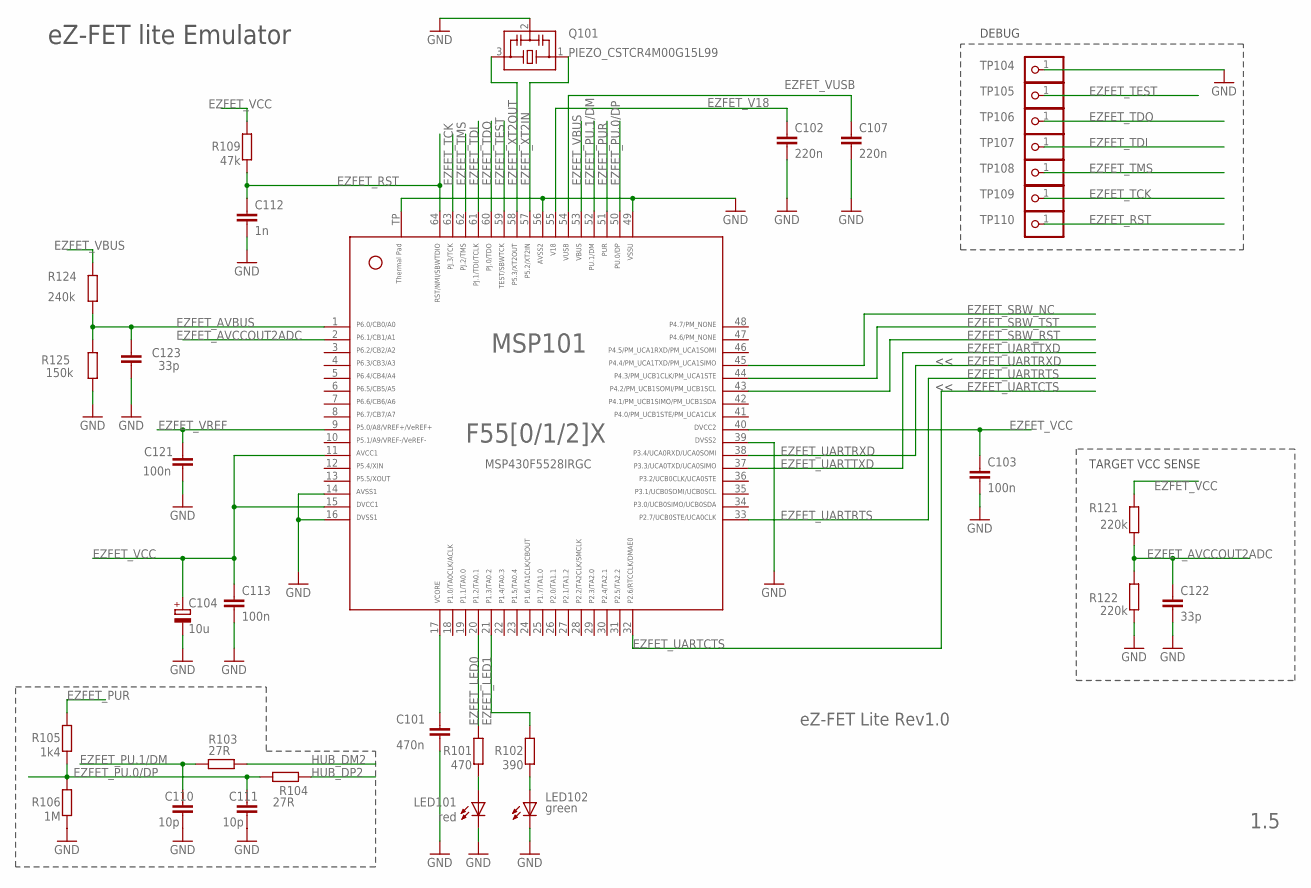
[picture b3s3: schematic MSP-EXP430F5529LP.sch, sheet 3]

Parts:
C101: 470n; C0402
C102, C107: 220n; C0402
C103, C113, C121: 100n; C0402
C104: 10u; A/3216-18R
C110, C111: 10p; C0402
C112: 1n; C0402
C122, C123: 33p; C0402
LED101: red; CHIP-LED0603
LED102: green; CHIP-LED0603
MSP101: MSP430F5528IRGC; RGC64
Q101: PIEZO_CSTCR4M00G15L99; MURATA-FILTER_CSTCR
R101: 470; R0402
R102: 390; R0402
R103, R104: 27R; R0402
R105: 1k4; R0402
R106: 1M; R0402
R109: 47k; R0402
R121, R122: 220k; R0402
R124: 240k; R0402
R125: 150k; R0402
TP104, TP105, TP106, TP107, TP108, TP109, TP110: TEST_PIN2; 1X01

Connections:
EZFET_AVBUS: C123.2, MSP101.1, R124.2, R125.1
EZFET_AVCCOUT2ADC: C122.2, MSP101.2, R121.2, R122.1
EZFET_LED0: MSP101.20, R101.2
EZFET_LED1: MSP101.21, R102.2
EZFET_PU.0/DP: C111.1, MSP101.50, R104.2, R105.1, R106.2
EZFET_PU.1/DM: C110.1, MSP101.52, R103.2
EZFET_PUR: MSP101.51, R105.2
EZFET_RST: C112.1, MSP101.64, R109.1, TP110.1
EZFET_SBW_NC: MSP101.45; also elsewhere on the board
EZFET_SBW_RST: MSP101.43; also elsewhere on the board
EZFET_SBW_TST: MSP101.44; also elsewhere on the board
EZFET_TCK: MSP101.63, TP109.1
EZFET_TDI: MSP101.61, TP107.1
EZFET_TDO: MSP101.60, TP106.1
EZFET_TEST: MSP101.59, TP105.1
EZFET_TMS: MSP101.62, TP108.1
EZFET_UARTCTS: MSP101.32; also elsewhere on the board
EZFET_UARTRTS: MSP101.33; also elsewhere on the board
EZFET_UARTRXD: MSP101.38; also elsewhere on the board
EZFET_UARTTXD: MSP101.37; also elsewhere on the board
EZFET_V18: C102.1, MSP101.55
EZFET_VBUS: MSP101.53, R124.1; also elsewhere on the board
EZFET_VCC: C103.1, C104.+, C113.1, MSP101.11, MSP101.15, MSP101.40, R109.2, R121.1; also elsewhere on the board
EZFET_VREF: C121.1, MSP101.9
EZFET_VUSB: C107.1, MSP101.54
EZFET_XT2IN: MSP101.57, Q101.1
EZFET_XT2OUT: MSP101.58, Q101.3
GND: C101.2, C102.2, C103.2, C104.-, C107.2, C110.2, C111.2, C112.2, C113.2, C121.2, C122.1, C123.1, LED101.C, LED102.C, MSP101.14, MSP101.16, MSP101.39, MSP101.49, MSP101.56, MSP101.TP, Q101.2, R106.1, R122.2, R125.2, TP104.1; also elsewhere on the board
HUB_DM2: R103.1; also elsewhere on the board
HUB_DP2: R104.1; also elsewhere on the board
unnamed: LED101.A, R101.1
unnamed: LED102.A, R102.1
unnamed: C101.1, MSP101.17

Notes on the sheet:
eZ-FET lite Emulator
MSP430F5528IRGC
TARGET VCC SENSE
eZ-FET Lite Rev1.0
1.5
DEBUG
